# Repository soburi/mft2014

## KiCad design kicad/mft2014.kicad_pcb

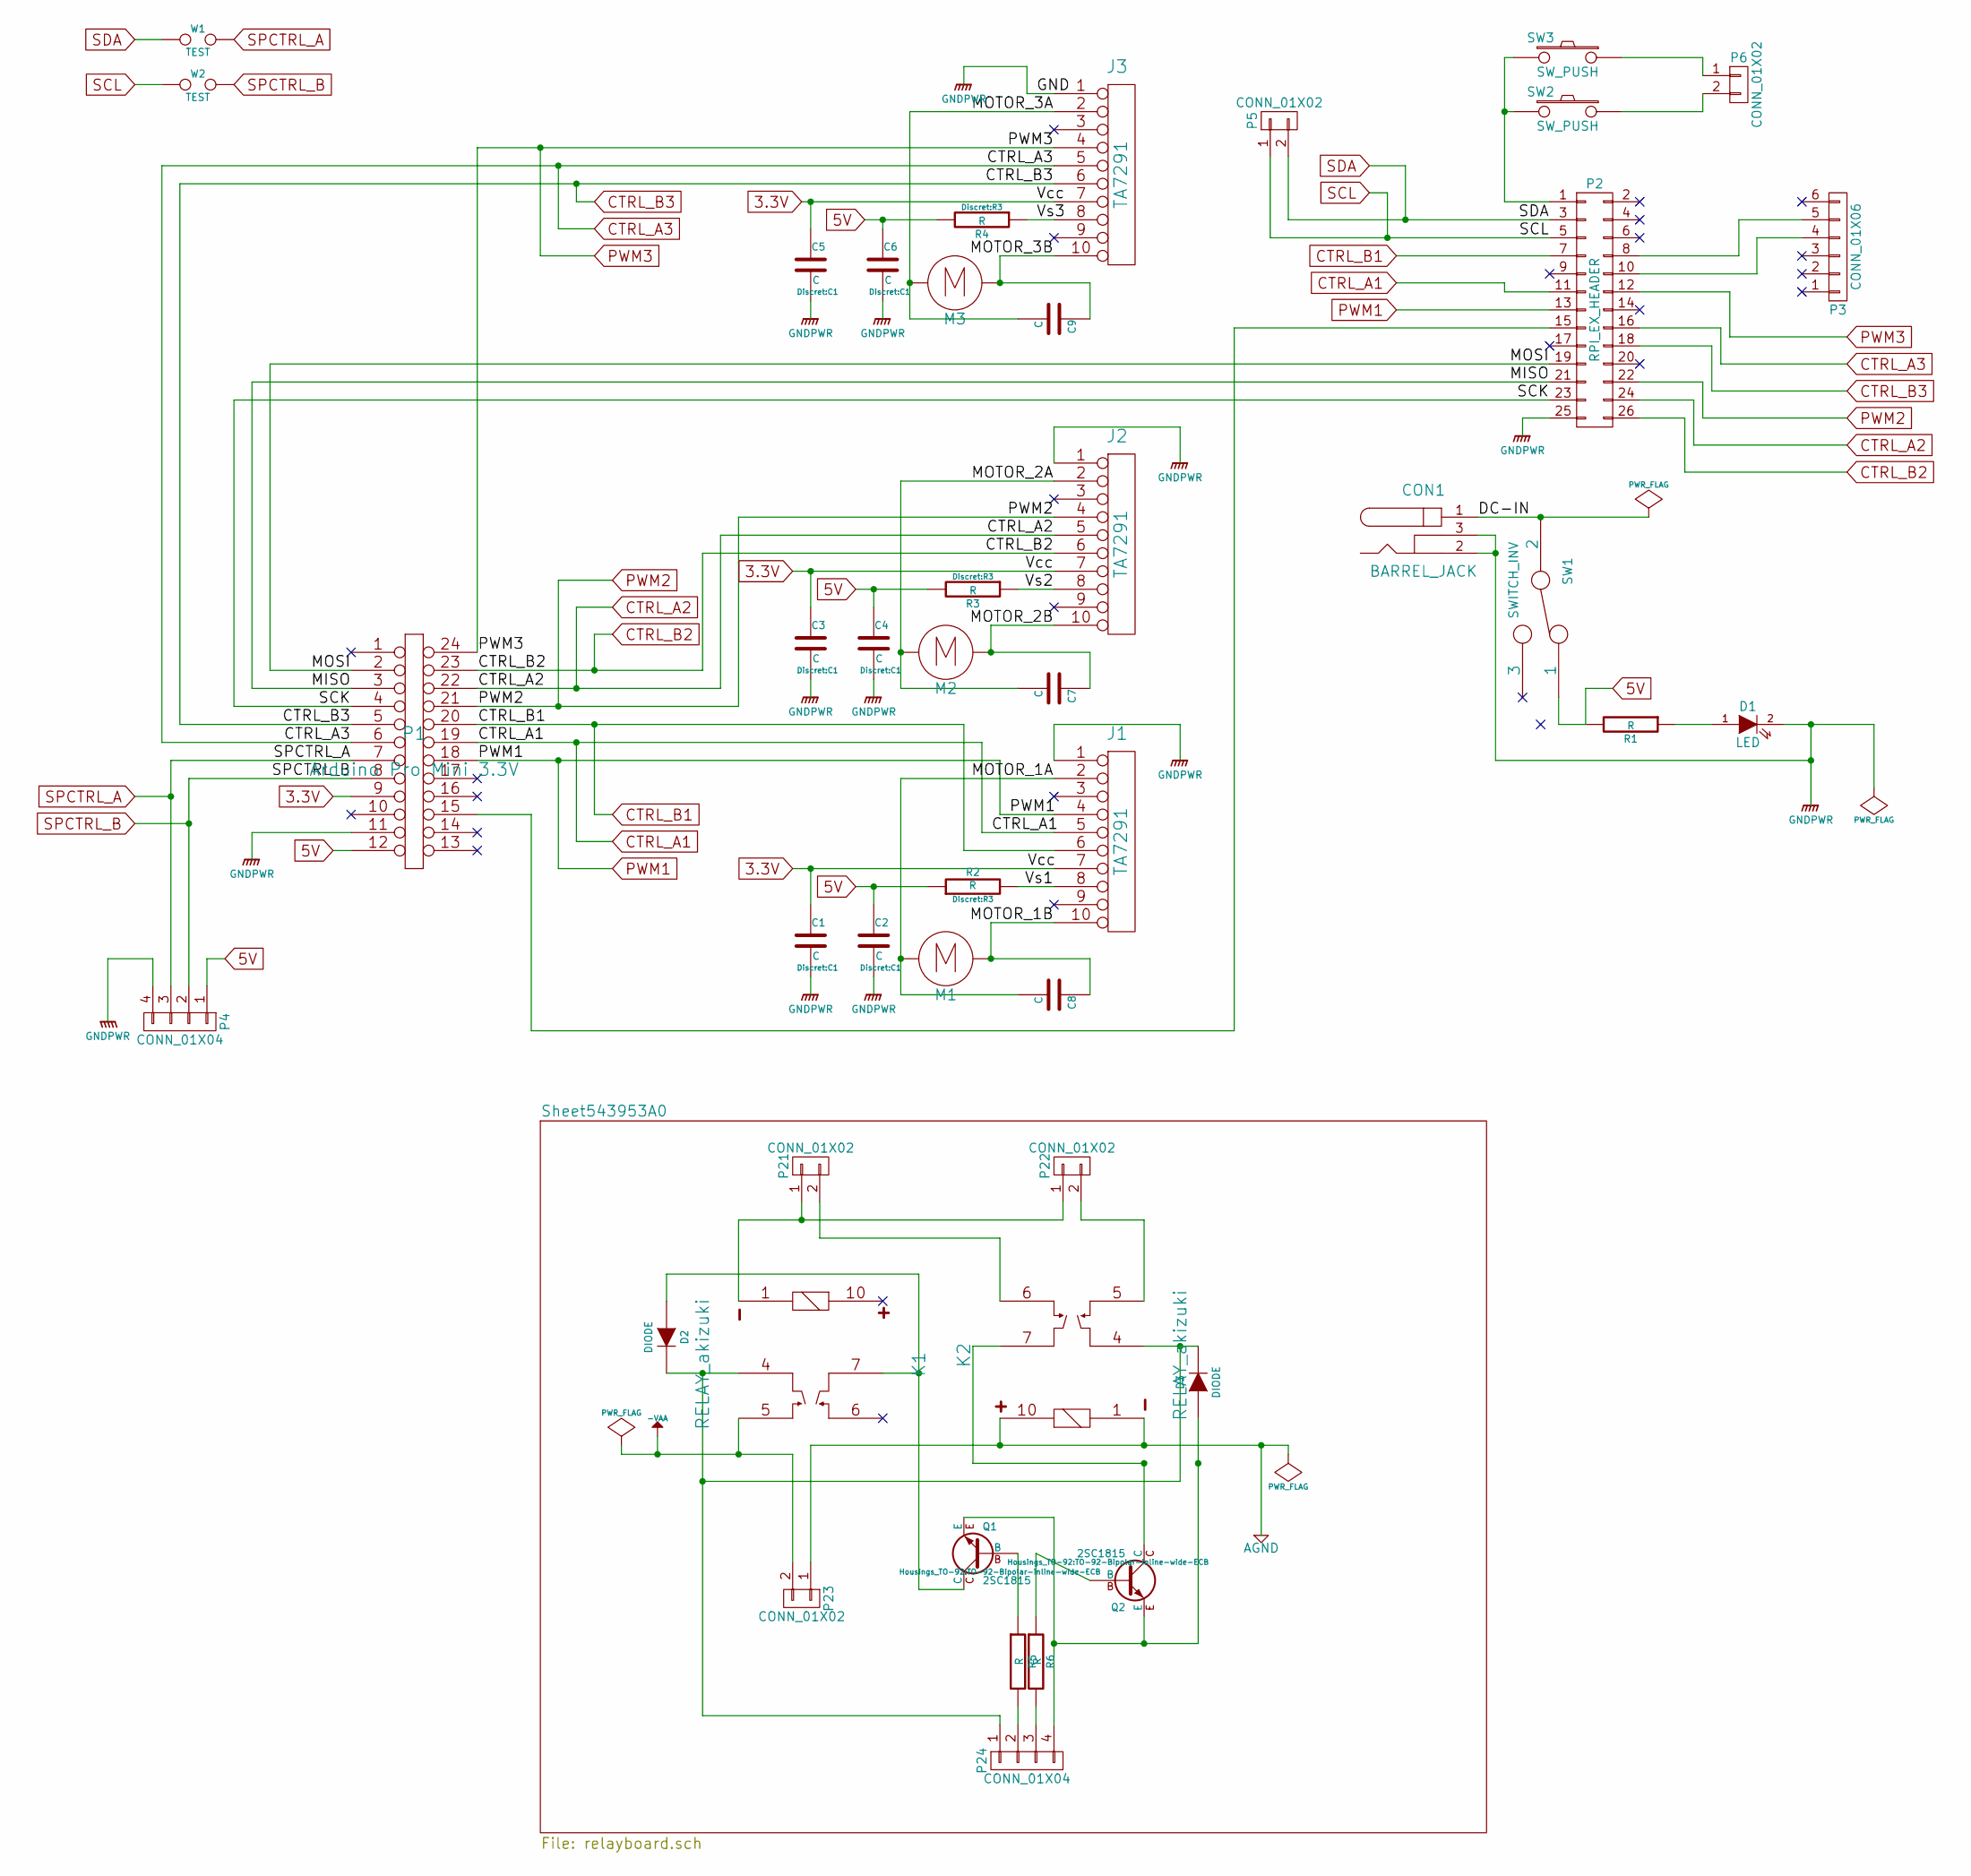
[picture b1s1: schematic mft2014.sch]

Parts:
C1, C2, C3, C4, C5, C6, C7, C8, C9: C; C1
CON1: BARREL_JACK
D1: LED; LED-3MM
D2, D3: DIODE; D3
J1, J2, J3: TA7291; Pin_Header_Straight_1x10
K1, K2: RELAY_akizuki; akizuki_relay
M1, M2, M3: dcmotor; Pin_Header_Straight_1x02
P1: Arduino Pro Mini 3.3V; DIP-24__600
P2: RPI_EX_HEADER; Pin_Header_Straight_1x04
P3: CONN_01X06; Pin_Header_Straight_1x06
P4: CONN_01X04; Pin_Header_Straight_2x13
P5, P6, P21, P22, P23: CONN_01X02; Pin_Header_Straight_1x02
P24: CONN_01X04; Socket_Strip_Straight_1x04
Q1, Q2: 2SC1815; TO-92-Bipolar-inline-wide-ECB
R1, R2, R3, R4, R5, R6: R; R3
SW1: SWITCH_INV; Pin_Header_Straight_1x03
SW2, SW3: SW_PUSH; C1V5
W1, W2: TEST; solder_jumper

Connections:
3.3V: C1.1, C3.1, C5.1, J1.7, J2.7, J3.7, P1.9
5V: C2.1, C4.1, C6.1, P1.12, P4.1, R1.2, R2.1, R3.2, R4.2, SW1.1
-VAA: K1.5, P23.2
/DC-IN: CON1.1, SW1.2
/MISO: P1.3, P2.21
/MOSI: P1.2, P2.19
/MOTOR_1A: C8.2, J1.2, M1.1
/MOTOR_1B: C8.1, J1.10, M1.2
/MOTOR_2A: C7.2, J2.2, M2.1
/MOTOR_2B: C7.1, J2.10, M2.2
/MOTOR_3A: C9.2, J3.2, M3.1
/MOTOR_3B: C9.1, J3.10, M3.2
/SCK: P1.4, P2.23
/Vs1: J1.8, R2.2
/Vs2: J2.8, R3.1
/Vs3: J3.8, R4.1
AGND: K2.1, K2.10, P23.1
CTRL_A1: J1.5, P1.19, P2.11
CTRL_A2: J2.5, P1.22, P2.24
CTRL_A3: J3.5, P1.6, P2.16
CTRL_B1: J1.6, P1.20, P2.7
CTRL_B2: J2.6, P1.23, P2.26
CTRL_B3: J3.6, P1.5, P2.18
GNDPWR: C1.2, C2.2, C3.2, C4.2, C5.2, C6.2, CON1.2, CON1.3, D1.2 (K), J1.1, J2.1, J3.1, P1.11, P2.25, P4.4
unnamed: D1.1 (A), R1.1
unnamed: D2.1 (A), K1.7, Q1.C
unnamed: D2.2 (K), D3.2 (K), K1.4, K2.4, P24.1
unnamed: D3.1 (A), P24.4, Q1.E, Q2.E
unnamed: K1.1, P21.1, P22.1
unnamed: K2.5, P22.2
unnamed: K2.6, P21.2
unnamed: K2.7, Q2.C
unnamed: P1.15, P2.15
unnamed: P2.1, SW2.2, SW3.2
unnamed: P2.8, P3.5
unnamed: P2.10, P3.4
unnamed: P6.1, SW3.1
unnamed: P6.2, SW2.1
unnamed: P24.2, R5.2
unnamed: P24.3, R6.2
unnamed: Q1.B, R5.1
unnamed: Q2.B, R6.1
PWM1: J1.4, P1.18, P2.13
PWM2: J2.4, P1.21, P2.22
PWM3: J3.4, P1.24, P2.12
SCL: P2.5, P5.1, W2.1
SDA: P2.3, P5.2, W1.1
SPCTRL_A: P1.7, P4.3, W1.2
SPCTRL_B: P1.8, P4.2, W2.2

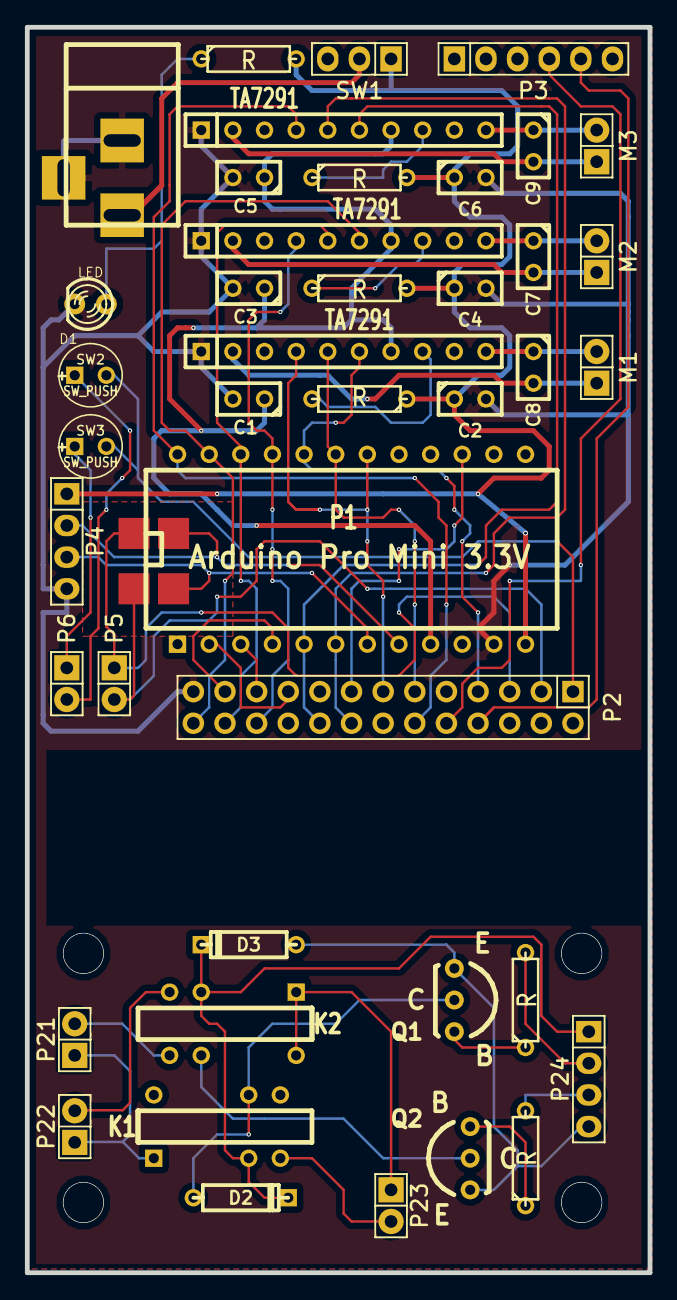
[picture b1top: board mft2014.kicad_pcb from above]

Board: 2 copper layers, 50.0 x 100.0 mm, 44 parts (0 on the bottom side), 49 nets.

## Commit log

2014-12-08 'mft2014ver'
